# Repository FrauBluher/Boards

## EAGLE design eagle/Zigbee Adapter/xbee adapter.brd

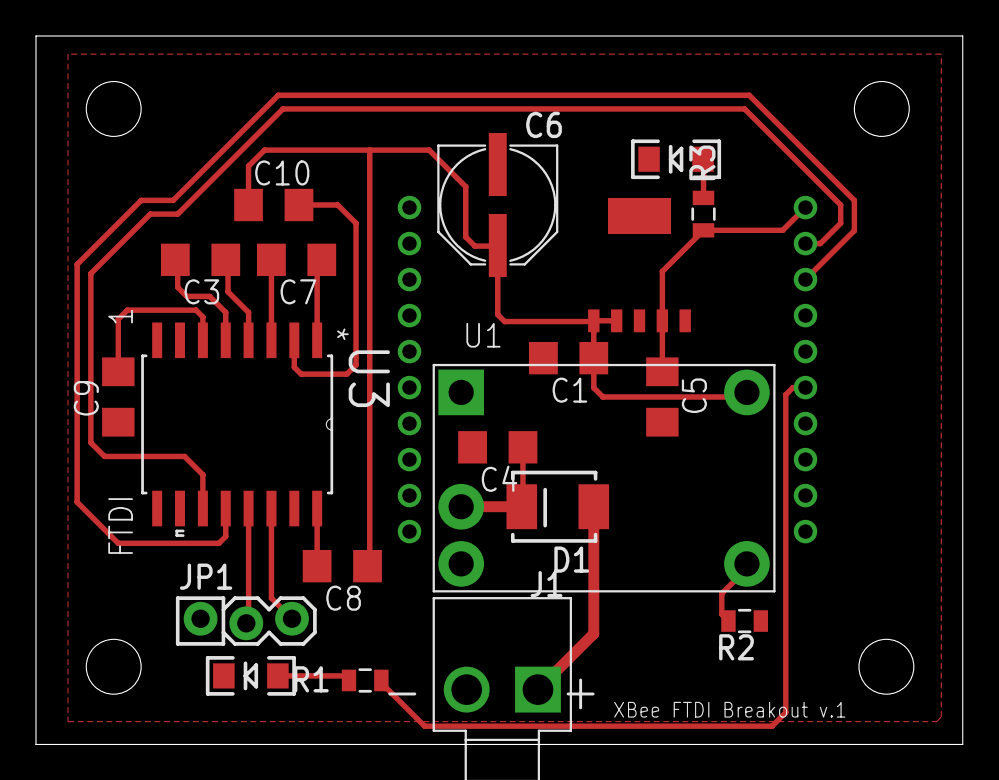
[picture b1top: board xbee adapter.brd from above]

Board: 2 copper layers, 51.5 x 39.4 mm, 25 parts (1 on the bottom side), 20 nets.

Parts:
C1: 4.7 uF; 1206
C3, C7, C8, C9, C10: 1206
C4: 2.2uF; 1206
C5: 1 uF; 1206
C6: 100uF; CPOL_6.6
D1: DIODE-SCHOTTKY240A; SMA-DIODE-B240A
E$1, E$2, E$3, E$4: STAND-OFF-TIGHT
J1: POW_CONNECTMALE; SOCKET-MALE-3.96MM-2
JP1: M03LOCK; 1X03_LOCK
LED1: ACT; LED-1206
LED2: PWR; LED-1206
R1, R3: 330; 0805
R2: 21k; 0805
U1: PTN78000
U3: MAX232DW; SOIC127P1030X265-16N
U$2: MCP1826; SOT223-5
XB1: XBEE-PRO

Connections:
GND: C1.2, C4.2, C5.2, C6.-, C9.1, J1.P$2, JP1.1, LED1.C, LED2.C, R2.1, U1.GND, U3.15, U$2.P$3, U$2.P$6, XB1.10
unnamed: C3.2, U3.5
unnamed: R1.1, XB1.6
unnamed: LED1.A, R1.2
unnamed: LED2.A, R3.1
unnamed: R2.2, U1.ADJ
unnamed: C7.2, U3.3
unnamed: C4.1, D1.C, U1.V_IN
unnamed: D1.A, J1.P$1
unnamed: C8.2, U3.16
unnamed: C9.2, U3.6
unnamed: C10.2, U3.2
unnamed: C3.1, U3.4
unnamed: C7.1, U3.1
RS232RX: JP1.2, U3.13
RS232TX: JP1.3, U3.14
RX: U3.12, XB1.3
TX: U3.11, XB1.2
VCC: C1.1, C6.+, C8.1, C10.1, U1.V_OUT, U$2.P$1, U$2.P$2
VCC3V3: C5.1, R3.2, U$2.P$4, XB1.1
